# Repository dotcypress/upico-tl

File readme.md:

## μPico Traffic Lights PMOD

## Resources

- [Schematics](docs/traffic-lights.pdf)
- [Gerbers](docs/upico_tl_rev0x01.zip)

## License

Licensed under either of

- Apache License, Version 2.0 ([LICENSE-APACHE](LICENSE-APACHE) or
  http://www.apache.org/licenses/LICENSE-2.0)
- MIT license ([LICENSE-MIT](LICENSE-MIT) or http://opensource.org/licenses/MIT)

at your option.

### Contribution

Unless you explicitly state otherwise, any contribution intentionally submitted
for inclusion in the work by you, as defined in the Apache-2.0 license, shall be
dual licensed as above, without any additional terms or conditions.

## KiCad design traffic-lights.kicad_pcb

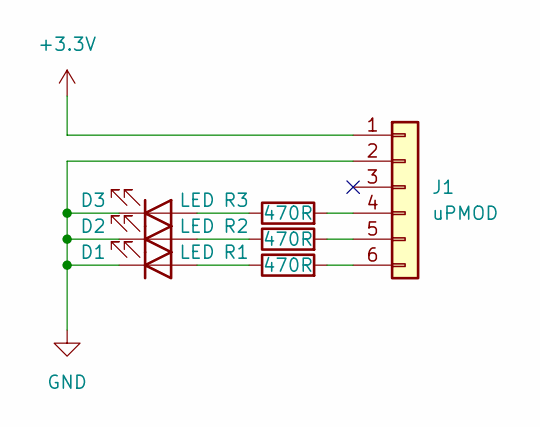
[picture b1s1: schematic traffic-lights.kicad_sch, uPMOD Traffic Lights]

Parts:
D1, D2, D3: LED; LED_Rectangular_W5.0mm_H5.0mm
J1: uPMOD; PinHeader_1x06_P2.54mm_Horizontal
R1, R2, R3: 470R; R_0603_1608Metric_Pad0.98x0.95mm_HandSolder

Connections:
+3.3V: J1.1
GND: D1.1 (K), D2.1 (K), D3.1 (K), J1.2
unnamed: D1.2 (A), R1.1
unnamed: D2.2 (A), R2.1
unnamed: D3.2 (A), R3.1
unnamed: J1.4, R3.2
unnamed: J1.5, R2.2
unnamed: J1.6, R1.2

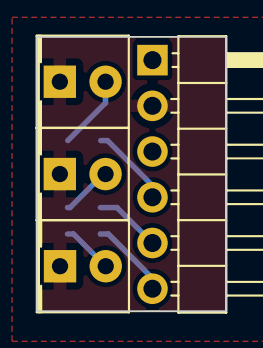
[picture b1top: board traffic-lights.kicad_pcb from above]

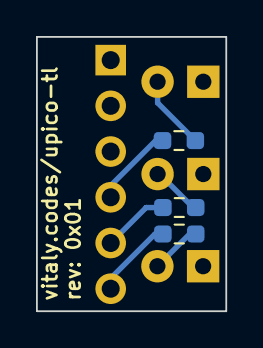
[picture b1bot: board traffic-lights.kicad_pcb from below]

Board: 2 copper layers, 10.5 x 15.2 mm, 7 parts (3 on the bottom side), 7 nets.

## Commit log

2023-10-16 rev: 0x01
2023-11-12 add readme
